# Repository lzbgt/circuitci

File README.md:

# CircuitCI

Agent-native embedded board validation runtime.

CircuitCI is a headless validation tool for embedded and IoT circuit designs. It
imports board artifacts, binds component models, runs deterministic validation
scenarios, and emits machine-readable reports that AI agents and engineers can
use before PCB fabrication.

It is not a schematic editor, PCB layout editor, or full EDA suite. The goal is
CI-style feedback for board designs: catch power, reset, boot, interface,
layout-evidence, and firmware-facing mistakes early enough that an agent or
engineer can fix the design and rerun validation.

## What It Does

- Parses Board IR YAML projects and component model libraries.
- Imports SPICE decks, KiCad XML netlists, native KiCad schematics, KiCad PCB
  placement/route evidence, JLC/EasyEDA BOM/CPL assembly evidence, Gerber
  board-outline/copper/solder-mask/solder-paste evidence, and Excellon/NC drill
  evidence.
- Suggests missing validation scenarios from board/model evidence.
- Validates power trees, regulator constraints, reset supervisors, boot straps,
  GPIO backdrive paths, I/O voltage compatibility, USB protection, USB route
  geometry, clocks, serial bootloaders, control-line sequences, and selected
  SPICE-backed analog checks.
- Writes stable JSON/Markdown reports with measurements, limits, severity, and
  suggested fixes.
- Keeps component behavior in data-driven model packs instead of hardcoding one
  MCU, USB-UART bridge, regulator, or board family into the engine.

## Current Scope

CircuitCI is currently an early Rust CLI focused on deterministic pre-fab board
validation. It already includes fixtures and model packs for common IoT-board
building blocks such as MCU boot/reset behavior, USB connectors, USB ESD
protection, LDO regulators, load switches, power muxes, battery chargers,
reset supervisors, USB-UART bridges, and level shifters.

The runtime deliberately reports limitations for areas it does not prove, such
as full USB PHY behavior, RF/antenna performance, complete PCB signal integrity,
thermal sign-off, arbitrary KiCad DRC semantics, and vendor-silicon internals.
See [docs/limitations.md](docs/limitations.md) and
[docs/common_iot_board_readiness_gaps.md](docs/common_iot_board_readiness_gaps.md).
For a concise engineering assessment of current practical value and boundaries,
see [docs/project_status_assessment.md](docs/project_status_assessment.md).
For the full-featured time/frequency-domain simulation research and backend
roadmap, see
[docs/research/circuit_simulation_full_featured/README.md](docs/research/circuit_simulation_full_featured/README.md).
For the prioritized backlog that makes CircuitCI more useful to board-validation
agents, see
[docs/agent_validation_usefulness_backlog.md](docs/agent_validation_usefulness_backlog.md).

## Install

Prerequisites:

- Rust toolchain with edition 2024 support.
- Optional: `ngspice` or `libngspice` for SPICE-backed analog scenarios.

Build:

```bash
cargo build --release
```

This creates the CLI at `target/release/circuitci`. Add it to your shell path
or call it directly from the repository:

```bash
export PATH="$PWD/target/release:$PATH"
circuitci --help
```

Run tests:

```bash
cargo test
cargo clippy --all-targets -- -D warnings
```

Optional native desktop GUI:

```bash
cargo run --features gui --bin circuitci-gui
```

The GUI is a Rust `egui`/`eframe` desktop shell with EDA-style workflow stages
for project loading, sketch/model review, scenario suggestions, validation,
simulation artifact observation, and report viewing. It uses the same engine as
the CLI and does not compile into default CLI builds. See
[docs/gui_frontend.md](docs/gui_frontend.md).

## CLI

Validate a Board IR project:

```bash
circuitci validate examples/good_power_tree_board/project.yaml \
  --output out/good_power_tree
```

Retain compact-model bundle import evidence during validation:

```bash
circuitci validate examples/good_power_tree_board/project.yaml \
  --output out/good_power_tree \
  --model-package-bundle-import \
    bundle=dist/tiny_resistor_bundle,install_dir=third_party/models/tiny_resistor,registry_output=third_party/models/compact_model_registry.json,max_runtime_ms=60000
```

Write a scenario suggestion artifact:

```bash
circuitci suggest-scenarios examples/scenario_suggestions_usb_connector_protection/project.yaml \
  --output out/scenario_suggestions.yaml
```

Add profile-coverage remediation templates for missing `iot_basic_v0` core
checks:

```bash
circuitci suggest-scenarios examples/good_backdrive_fixed_board/project.yaml \
  --profile iot_basic_v0 \
  --output out/profile_suggestions.yaml
```

Import a KiCad schematic:

```bash
circuitci import-kicad-schematic path/to/root.kicad_sch \
  --mapping path/to/circuitci.kicad-map.yaml \
  --output out/imported.project.yaml
```

Enrich an imported project with KiCad PCB placement and route evidence:

```bash
circuitci import-kicad-pcb path/to/board.kicad_pcb \
  --project out/imported.project.yaml \
  --output out/imported_with_layout.project.yaml
```

Import JLC/EasyEDA assembly BOM and placement evidence:

```bash
circuitci import-jlc-assembly \
  --bom path/to/bom.csv \
  --placement path/to/placement.csv \
  --output out/imported_assembly.project.yaml
```

Inspect an EasyEDA Pro `.eprj2` SQLite project envelope:

```bash
circuitci inspect-easyeda-pro path/to/project.eprj2 \
  --output out/easyeda_pro_inspection.md
```

Append EasyEDA/JLC flying-probe pad and net evidence:

```bash
circuitci import-easyeda-flying-probe path/to/FlyingProbeTesting.json \
  --project out/imported_assembly.project.yaml \
  --output out/imported_with_probe_pads.project.yaml
```

Enrich an imported project with Gerber board-outline evidence:

```bash
circuitci import-gerber-outline path/to/Gerber_BoardOutlineLayer.GKO \
  --project out/imported_assembly.project.yaml \
  --output out/imported_with_outline.project.yaml
```

Append Gerber copper evidence:

```bash
circuitci import-gerber-copper path/to/Gerber_TopLayer.GTL \
  --project out/imported_with_outline.project.yaml \
  --output out/imported_with_copper.project.yaml
```

Append Gerber solder-mask evidence:

```bash
circuitci import-gerber-solder-mask path/to/Gerber_TopSolderMaskLayer.GTS \
  --project out/imported_with_copper.project.yaml \
  --output out/imported_with_mask.project.yaml
```

Append Gerber solder-paste evidence:

```bash
circuitci import-gerber-solder-paste path/to/Gerber_TopPasteMaskLayer.GTP \
  --project out/imported_with_mask.project.yaml \
  --output out/imported_with_paste.project.yaml
```

Append Excellon/NC drill evidence:

```bash
circuitci import-excellon-drill path/to/Drill_PTH_Through.DRL \
  --project out/imported_with_paste.project.yaml \
  --output out/imported_with_drills.project.yaml

circuitci import-excellon-drill path/to/Drill_PTH_Through_Via.DRL \
  --project out/imported_with_drills.project.yaml \
  --output out/imported_with_drills_and_vias.project.yaml
```

Attach explicit order/manufacturing metadata when those values are known from
the fabrication order, stencil order, or another reviewed process record:

```bash
circuitci set-manufacturing-metadata out/imported_with_drills_and_vias.project.yaml \
  --output out/imported_with_order_metadata.project.yaml \
  --stencil-thickness-mm 0.10 \
  --min-drill-edge-clearance-mm 0.50 \
  --min-slot-edge-clearance-mm 0.50 \
  --min-paste-area-ratio 0.70 \
  --max-paste-area-ratio 1.00 \
  --min-solder-paste-spacing-mm 0.15 \
  --source jlc_order_metadata
```

Or import the same reviewed facts from a source CSV while preserving row-level
evidence in a JSON manifest. Repeated `field=controlled_impedance_net` and
`field=controlled_impedance_pair` rows create or replace reviewed
`board.manufacturing.controlled_impedance` targets, including optional
solder-mask loading metadata, repeated `field=controlled_impedance_coupon`
rows create or replace reviewed fabricator coupon measurement evidence that
validation maps back to matching reviewed board impedance targets, repeated
`field=controlled_impedance_coupon_sample` rows attach reviewed coupon batch
sample measurements under named coupons, and coupon rows can carry reviewed
lot/panel/stackup plus trace layer/width/gap correlation metadata. Repeated
`field=controlled_impedance_solver_result` rows create or replace reviewed
source-backed solver-result evidence under
`board.manufacturing.controlled_impedance.solver_results[]`, and repeated
`field=controlled_impedance_solver_sample` rows attach reviewed solver
sweep/corner samples under named solver results. Solver-result rows can also
carry reviewed signed-artifact URI/digest/signer metadata, input-deck
URI/digest, output-schema URI/digest, reviewed solver configuration-lock
URI/digest/tool/revision metadata, reviewed runtime allowlist/profile/options
metadata, reviewed license/feature entitlement metadata, reviewed execution
environment lock/fingerprint metadata, reviewed run-log/random-seed/numeric
tolerance metadata, setup metadata, copper-roughness metadata,
etch-compensation metadata, and material-library
metadata for consistency screening. Repeated
`field=controlled_impedance_solver_material_corner` rows attach reviewed
dielectric material/corner evidence under named solver results, tying required
solver corners back to explicit stackup material metadata. Repeated
`field=controlled_impedance_solver_material_library` rows record reviewed
material-library artifact content and required field coverage, and repeated
`field=controlled_impedance_solver_material_acceptance` rows record reviewed
fabricator acceptance of solver material library/revision and stackup revision
coverage. Repeated `field=controlled_impedance_solver_material_process` rows
record reviewed material lot/process drift evidence for solver material
library/revision, fabricator stackup revision, dielectric layer, and material.
Repeated `field=controlled_impedance_solver_runtime_allowlist` rows record
reviewed runtime option allowlists for a solver and configuration-lock
revision.
Repeated `field=controlled_impedance_solver_entitlement` rows record reviewed
solver license/feature entitlement evidence for a solver and tool version.
Repeated `field=controlled_impedance_solver_execution_environment` rows record
reviewed solver execution environment lock evidence, including artifact
provenance, a reproducibility fingerprint, and locked component names.
Repeated `field=controlled_impedance_solver_run_log` rows record reviewed
solver run-log reproducibility evidence, including artifact provenance, run
id, random seed, numeric tolerance policy, residual limit, and iteration
limit. Optional rerun limits on that row can require reviewed deterministic
rerun samples imported with repeated `field=controlled_impedance_solver_rerun`
rows. Optional convergence-window limits on the run-log row can require
reviewed solver convergence samples imported with repeated
`field=controlled_impedance_solver_convergence_sample` rows, including
stopping criteria, residual, iteration, artifact URI, and artifact digest
evidence. A run-log row can also opt into monotonic residual trend evidence
with `require_monotonic_residual_decrease`, and can carry reviewed numerical
precision policy provenance such as floating-point format, significant digits,
roundoff budget, artifact URI, and artifact digest.
Repeated
`field=controlled_impedance_solver_qualification` rows create or replace
reviewed solver tool/version qualification evidence. Repeated
`field=thermal_copper` rows create or replace reviewed
`board.manufacturing.thermal_copper[]` policy entries, and repeated
`field=thermal_measurement` rows append reviewed measured-temperature evidence
under `board.manufacturing.thermal_measurements[]`. Repeated
`field=thermal_package` rows create or replace reviewed component package
thermal metadata under `board.manufacturing.thermal_packages[]`. Repeated
`field=thermal_environment` rows create or replace reviewed operating
environment evidence under `board.manufacturing.thermal_environments[]`.
Repeated `field=thermal_limit` rows create or replace reviewed measured and
package temperature limits under `board.manufacturing.thermal_limits[]`.
Repeated
`field=stackup_layer` rows create or replace reviewed
`board.layout.stackup.layers[]` entries so stackup evidence can travel with
fabrication/order metadata without hand-authored YAML. Repeated
`field=rf_antenna_keepout`, `field=rf_antenna_feed_path`,
`field=rf_antenna_matching_network`, `field=rf_antenna_measurement`, and
`field=rf_antenna_performance_limit` rows create or replace reviewed RF
antenna layout/topology/measurement/limit constraints, including optional
sampled sweep-coverage policy and measurement-condition evidence, under
`board.layout.constraints.rf_antenna`:

```bash
circuitci import-manufacturing-metadata \
  --project out/imported_with_drills_and_vias.project.yaml \
  --metadata order_metadata.csv \
  --output out/imported_with_order_metadata.project.yaml \
  --source jlc_order_metadata \
  --allow-unknown-fields
```

`suggest-scenarios` consumes these Board IR fields to make matching
manufacturing templates runnable without turning order-specific limits into
global process defaults.

Run an acceptance suite:

```bash
circuitci validate-suite suites/um_stm32l4_downloader_acceptance.yaml \
  --output out/acceptance
```

## Project Model

CircuitCI uses a normalized Board IR:

```text
project.yaml / KiCad / SPICE
  -> Board Graph IR
  -> component model binding
  -> scenario execution
  -> validation rules and optional SPICE backend
  -> JSON + Markdown reports
```

Important contracts:

- [docs/current_capabilities.md](docs/current_capabilities.md)
- [docs/board_ir.md](docs/board_ir.md)
- [docs/component_model_contract.md](docs/component_model_contract.md)
- [docs/scenario_language.md](docs/scenario_language.md)
- [docs/fabrication_process_presets.md](docs/fabrication_process_presets.md)
- [docs/manufacturing_metadata_importer.md](docs/manufacturing_metadata_importer.md)
- [docs/gui_frontend.md](docs/gui_frontend.md)
- [docs/report_schema.md](docs/report_schema.md)
- [docs/scenario_suggestions.md](docs/scenario_suggestions.md)

## Repository Layout

```text
src/
  board_ir/       Board IR parsing and normalized project types
  cli/            Command-line entry points
  gui.rs          Optional Rust desktop frontend behind the gui feature
  importers/      KiCad, SPICE, and layout-evidence importers
  library/        Component model loading and binding
  reports/        JSON and Markdown report generation
  validation/     Deterministic rule implementations

libs/
  generic/        Generic component models
  vendor/         Datasheet-backed vendor model packs

models/spice/     SHA-pinned SPICE model cards and generic behavioral
                  macro-model libraries used by generated analog scenarios
examples/         Passing/failing fixtures and importer demos
schemas/          JSON schemas for Board IR and reports
suites/           Acceptance-suite manifests
tests/            CLI and integration regressions
docs/             Engineering contracts and research notes
```

## Validation Philosophy

CircuitCI is conservative:

- A rule fails closed when required evidence is missing.
- Reports distinguish proven failures from low-confidence or unmodeled areas.
- Datasheet-backed component packs record their source artifacts and modeled
  facts.
- Suggestions never invent observations such as reset-release timestamps,
  strap states, protection resistance, load-switch enable state, or board layout
  limits.

## License

MIT. See [LICENSE](LICENSE).

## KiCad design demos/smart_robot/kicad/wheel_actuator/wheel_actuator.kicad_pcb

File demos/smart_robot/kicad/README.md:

# Smart Robot KiCad CAD Bridge

This folder contains KiCad-source artifacts that are meant to be imported back
through CircuitCI during schematic/layout iteration.

## Motion Core

`motion_core/root.kicad_sch` is the first KiCad schematic skeleton for the
validated motion-core logical model. It intentionally uses local `CircuitCI:*`
symbols with named pins so agents can edit connectivity without depending on a
complete production symbol library yet.

`motion_core/circuitci.kicad-map.yaml` binds those schematic references and
pins back to the same source-backed models used by
`../circuitci/motion_core/project.yaml`.

Current scope:

- LicheeRV Nano purchased module interface.
- AT32F435 motion MCU.
- ICM-42688-P IMU SPI/interrupt link.
- TCAN3413 CAN transceiver.
- THVD1450 RS485 transceiver.
- ESD2CAN24-Q1 and ESDS552 static bus TVS devices.
- 120 ohm CAN and RS485 endpoint termination options.

Import check:

```sh
circuitci import-kicad-schematic \
  demos/smart_robot/kicad/motion_core/root.kicad_sch \
  --mapping demos/smart_robot/kicad/motion_core/circuitci.kicad-map.yaml \
  --output out/smart_robot_motion_core_imported.project.yaml
```

The imported Board IR is a connectivity source artifact. It does not yet carry
all fields from the richer logical validation model, such as `power_domains`,
validation scenarios, pre-layout placement contracts, or routed PCB evidence.
Keep using `../circuitci/motion_core/project.yaml` for sign-off checks until
the KiCad importer round-trips those fields or explicit overlay steps are
added.

## Wheel Actuator

`wheel_actuator/root.kicad_sch` is the matching KiCad connectivity skeleton for
the reusable left/right wheel actuator board. It uses local `CircuitCI:*`
symbols for the motor-control MCU, DRV8323 gate driver, CAN transceiver and TVS,
endpoint termination option, encoder/Hall input, preliminary CSD88599Q5DC
three-phase bridge candidate, phase shunts, motor-load envelope, regeneration
absorber envelope, and JST VH actuator-bus connector.

`wheel_actuator/circuitci.kicad-map.yaml` binds those schematic references and
pins back to the source-backed models used by
`../circuitci/wheel_actuator/project.yaml`. It also carries the
`MODEL_QUALITY_REQUIRED` sign-off scenario for `M1`, plus the
`LOAD_CABLE_CURRENT_VALID`, `LOAD_CABLE_THERMAL_DERATING_VALID`, and
`LOAD_CABLE_VOLTAGE_DROP_VALID` actuator-bus harness gates. The imported
schematic carries selected JST VH/AWG16 harness current and loop-resistance
evidence and selected Vishay RH100 first-pass regen absorber evidence, but
still blocks fabrication until the placeholder motor and cable
temperature-rise evidence are replaced by selected datasheet or measured
evidence.

`wheel_actuator/wheel_actuator.kicad_pcb` is the first smart-robot PCB layout
bridge. It is a compact placement/routing artifact for import testing: it
contains component placements, JACT1 CAN and power pads, CAN ESD/termination
placement, preliminary motor bridge, phase-shunt and motor pads, CAN routes,
motor power/phase routes, current-sense routes, a ground zone, and explicit
net-class constraints.

Import check:

```sh
circuitci import-kicad-schematic \
  demos/smart_robot/kicad/wheel_actuator/root.kicad_sch \
  --mapping demos/smart_robot/kicad/wheel_actuator/circuitci.kicad-map.yaml \
  --output out/smart_robot_wheel_actuator_imported.project.yaml

circuitci import-kicad-pcb \
  demos/smart_robot/kicad/wheel_actuator/wheel_actuator.kicad_pcb \
  --project out/smart_robot_wheel_actuator_imported.project.yaml \
  --output out/smart_robot_wheel_actuator_with_pcb.project.yaml
```

As with the motion-core bridge, the imported schematic Board IR proves
connectivity and model binding only. The PCB-enriched Board IR additionally
proves first-pass placement, pad, route, via, outline, zone, and routing-rule
evidence. The imported route widths now also drive the wheel actuator CAN
placement checks and first-pass motor phase/`VBAT_SW` route-current checks. It
also drives the first-pass phase-shunt and current-sense route placement
checks. It is still not a final layout sign-off: it does not prove MOSFET
SOA/thermal margins, dynamic current-sense waveform behavior, copper
temperature rise, selected regeneration absorber behavior, repeated-pulse
heating, selected cable assembly current/thermal/drop behavior, EMC, or
manufacturing DRC.

## PMU

`pmu/root.kicad_sch` is the KiCad connectivity skeleton for the reusable PMU
board. It uses local `CircuitCI:*` symbols for the USB-C PD source placeholder,
protected 2S battery source, BQ25798 charger, TPS54331 5 V buck, TPS62162
3.3 V buck, required 3.3 V support passives, selected TPS25948 servo switch,
selected TPS24751/CSD17501Q5A wheel switch path, and the first-pass rail load
budgets.

`pmu/circuitci.kicad-map.yaml` binds those schematic references and pins back
to the source-backed models used by `../circuitci/pmu/project.yaml`. It also
preserves the selected TPS25948 model for `U_SERVO_SW`, the selected
TPS24751/CSD17501Q5A path for `U_WHEEL_SW`, and the
`MODEL_QUALITY_REQUIRED` gate for both switched rails. It
also preserves the `POWER_SWITCH_BUDGET_VALID`, reverse-current, and inrush
gates, so imported schematics cannot bypass selected-part current-limit,
static thermal, reverse-mode, and soft-start evidence requirements.

Import check:

```sh
circuitci import-kicad-schematic \
  demos/smart_robot/kicad/pmu/root.kicad_sch \
  --mapping demos/smart_robot/kicad/pmu/circuitci.kicad-map.yaml \
  --output out/smart_robot_pmu_imported.project.yaml
```

The imported Board IR proves PMU connectivity, passive values, and the
selected-switch sign-off gate only. It does not yet round-trip the BQ25798
configured charge current, power-domain metadata, e-stop pin states, regulator
layout contracts, selected-switch current/thermal behavior, or routed PCB
evidence.

## Servo Payload

`servo_payload/root.kicad_sch` is the KiCad connectivity skeleton for the
low-load PWM servo/payload board. It uses local `CircuitCI:*` symbols for the
AT32F435 I2C/OE host pins, PCA9685 PWM driver, four low-load servo design
loads, and four JST XH servo headers.

`servo_payload/circuitci.kicad-map.yaml` binds those schematic references and
pins back to the source-backed models used by
`../circuitci/servo_payload/project.yaml`.

Import check:

```sh
circuitci import-kicad-schematic \
  demos/smart_robot/kicad/servo_payload/root.kicad_sch \
  --mapping demos/smart_robot/kicad/servo_payload/circuitci.kicad-map.yaml \
  --output out/smart_robot_servo_payload_imported.project.yaml
```

The imported Board IR proves I2C, OE, PWM fanout, servo power, and connector
signal connectivity only. It does not yet round-trip connector-current budget
scenarios, servo stall/regeneration assumptions, cable assembly derating, or
routed PCB evidence.

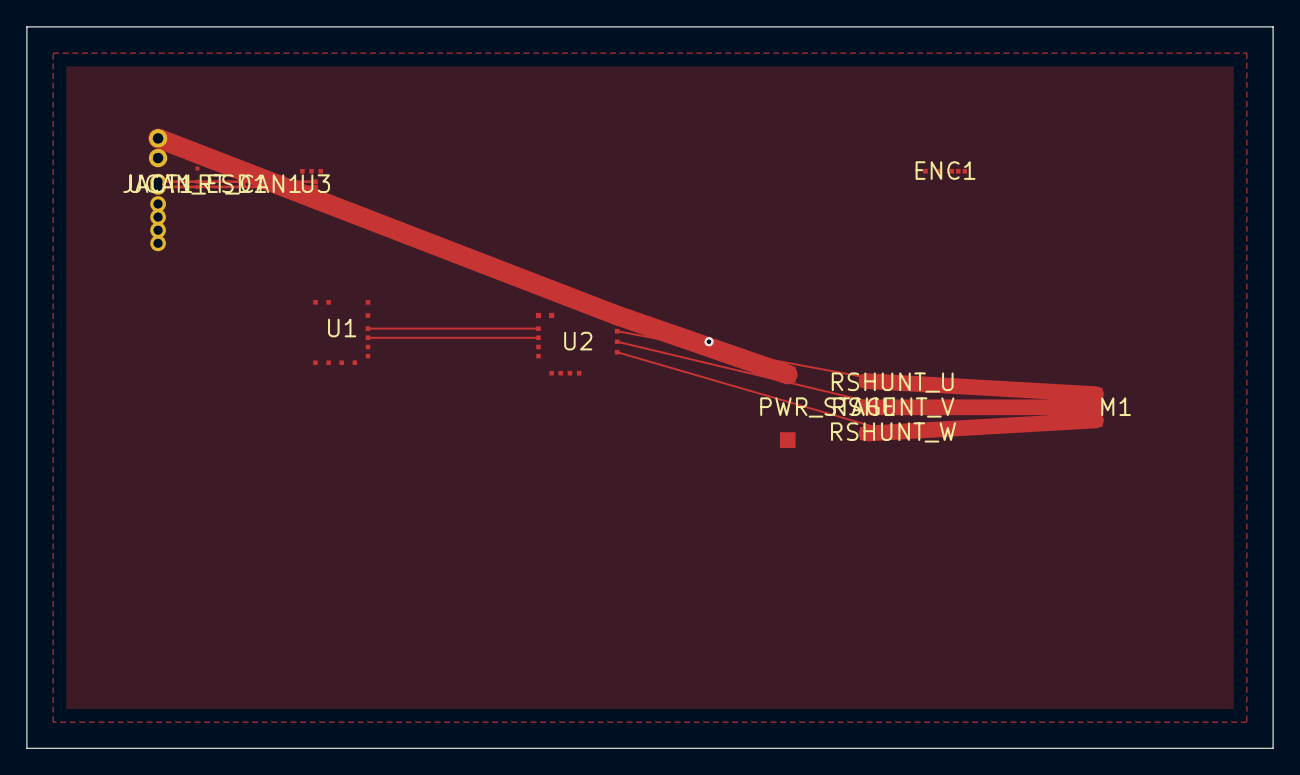
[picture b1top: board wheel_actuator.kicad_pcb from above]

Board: 0 copper layers, 95.0 x 55.0 mm, 12 parts (0 on the bottom side), 21 nets.

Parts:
ENC1: ENCODER_OR_HALL_3V3; Encoder_Hall_3V3
JACT1: B8P-VH_ACTUATOR_BUS; JST_VH_8Pin_Actuator_Bus
M1: WHEEL_MOTOR_DESIGN_ENVELOPE; Wheel_Motor_Envelope
PWR_STAGE: 3x_CSD88599Q5DC_PRELIMINARY; CSD88599Q5DC_3Phase_Bridge
RSHUNT_U: 5mR_1W; Phase_Shunt_5mR
RSHUNT_V: 5mR_1W; Phase_Shunt_5mR
RSHUNT_W: 5mR_1W; Phase_Shunt_5mR
RT_CAN1: 120R; CAN_Termination
U1: AT32M416; AT32M416_Motor_Control
U2: DRV8323
U3: TCAN3413DR; TCAN3413
UCAN_ESD1: ESD2CAN24-Q1; ESD2CAN24_Q1

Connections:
3v3_logic: ENC1.VCC, U1.VDD, U2.DVDD, U3.VCC, U3.VIO
cur_u: RSHUNT_U.B, U2.SOA
cur_v: RSHUNT_V.B, U2.SOB
cur_w: RSHUNT_W.B, U2.SOC
drv_enable: U1.DRV_EN, U2.ENABLE
drv_inha: U1.PWM_UH, U2.INHA
drv_inhb: U1.PWM_VH, U2.INHB
drv_inhc: U1.PWM_WH, U2.INHC
drv_inla: U1.PWM_UL, U2.INLA
drv_inlb: U1.PWM_VL, U2.INLB
drv_inlc: U1.PWM_WL, U2.INLC
drv_nfault: U1.DRV_NFAULT, U2.NFAULT
gnd: ENC1.GND, JACT1.GND, PWR_STAGE.GND, U1.GND, U2.GND, U3.GND, UCAN_ESD1.GND
phase_u: M1.PHASE_U, PWR_STAGE.PHASE_U, RSHUNT_U.A
phase_v: M1.PHASE_V, PWR_STAGE.PHASE_V, RSHUNT_V.A
phase_w: M1.PHASE_W, PWR_STAGE.PHASE_W, RSHUNT_W.A
robot_canh: JACT1.CANH, RT_CAN1.A, U3.CANH, UCAN_ESD1.CANH
robot_canl: JACT1.CANL, RT_CAN1.B, U3.CANL, UCAN_ESD1.CANL
vwheel_sw: JACT1.VBAT, PWR_STAGE.VM, U2.VM
wheel_can_rx: U1.CAN_RX, U3.RXD
wheel_can_tx: U1.CAN_TX, U3.TXD

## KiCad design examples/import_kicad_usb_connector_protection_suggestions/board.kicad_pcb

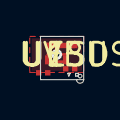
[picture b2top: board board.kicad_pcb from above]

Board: 0 copper layers, 2.4 x 2.4 mm, 4 parts (0 on the bottom side), 4 nets.

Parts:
H1: NPTH
J1: USB2_CONNECTOR; USB2
UESD: TPD2EUSB30
UVBUS: VBUS_ESD

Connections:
GND: J1.GND, J1.SHIELD, UESD.GND, UVBUS.GND
USB_DM: J1.D-, UESD.D1-
USB_DP: J1.D+, UESD.D1+
USB_VBUS: J1.VBUS, UVBUS.IO

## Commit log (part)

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2026-06-28 Add missing-net YAML repair
2026-06-28 Add stray-pin YAML repair
2026-06-28 Report blocked YAML repairs
2026-06-28 Add YAML repair dry-run mode
2026-06-28 Add report-driven YAML repair apply
2026-06-28 Add selective YAML repair proposal apply
2026-06-28 Add required-pin YAML repair
2026-06-28 Add YAML repair reason codes
2026-06-28 Preserve EasyEDA pad source evidence
2026-06-28 Add EasyEDA Pro inspection manifest
2026-06-28 Add JLC assembly import manifest
2026-06-28 Add KiCad footprint semantic evidence
2026-06-28 Sync footprint import backlog
2026-06-28 Preserve KiCad pad fabrication overrides
2026-06-28 Add EasyEDA Pro structure object evidence
2026-06-28 Classify EasyEDA Pro plaintext payload shapes
2026-06-28 Add manufacturing metadata CSV import
2026-06-28 Add JLC assembly orientation evidence
2026-06-28 Preserve KiCad footprint property evidence
2026-06-28 Add assembly footprint alignment validation
2026-06-28 Suggest assembly footprint alignment checks
2026-06-28 Add pin 1 orientation validation
2026-06-28 Add conductor creepage clearance validation
2026-06-28 Add controlled impedance geometry validation
2026-06-28 Add adjacent plane return path validation
2026-06-28 Suggest adjacent plane return path checks
2026-06-28 Add reference plane slot crossing validation
2026-06-28 Suggest reference plane slot crossing checks
2026-06-28 Add return path stitching via validation
2026-06-28 Suggest return path stitching via checks
2026-06-28 Suggest controlled impedance geometry checks
2026-06-28 Split manufacturing route physics suggestions
2026-06-28 Split manufacturing scenario suggestion tests
2026-06-28 Add controlled impedance stackup evidence checks
2026-06-28 Add RF antenna keepout validation
2026-06-28 Add RF antenna feed path validation
2026-06-28 Add thermal copper area validation
2026-06-28 Add thermal via stackup validation
2026-06-28 Add thermal package temperature validation
2026-06-28 Add measured thermal validation evidence
2026-06-28 Add thermal via plating validation
2026-06-28 Split thermal manufacturing modules
2026-06-28 Add thermal measurement uncertainty margins
2026-06-28 Add thermal derating environment validation
2026-06-28 Add thermal via plating thickness evidence
2026-06-28 Add thermal via barrel cross-section validation
2026-06-28 Add thermal copper metadata CSV import
2026-06-28 Add controlled impedance metadata CSV import
2026-06-28 Split manufacturing metadata row parsing
2026-06-28 Add stackup layer metadata CSV import
2026-06-28 Add RF antenna metadata CSV import
2026-06-28 Split manufacturing metadata CSV parsing
2026-06-28 Split manufacturing metadata row families
2026-06-28 Add reviewed thermal package metadata import
2026-06-28 Check conflicting thermal package metadata
2026-06-28 Add thermal environment metadata import
2026-06-28 Add thermal limit metadata import
2026-06-28 Add RF measured performance validation
2026-06-28 Add RF antenna measurement metadata import
2026-06-28 Add RF matching topology validation
2026-06-28 Add RF matching metadata CSV import
2026-06-28 Update RF layout physics backlog
2026-06-28 Add RF performance limit metadata import
2026-06-28 Add RF sweep performance evidence
2026-06-28 Split RF antenna measurement validation
2026-06-28 Add RF measurement condition evidence
2026-06-29 Split RF antenna scenario suggestions
2026-06-29 Add controlled impedance solder mask validation
2026-06-29 Add controlled impedance coupon validation
2026-06-29 Split RF manufacturing metadata tests
2026-06-29 Improve imported schematic readability
2026-06-29 Map impedance coupons to board targets
2026-06-29 Clarify impedance coupon mapping guidance
2026-06-29 Add impedance coupon batch validation
2026-06-29 Add impedance coupon trace correlation validation
2026-06-29 Add controlled impedance solver result validation
2026-06-29 Split controlled impedance suggestions
2026-06-29 Add solver artifact provenance evidence
2026-06-29 Add impedance solver sweep evidence
2026-06-29 Add solver input deck consistency evidence
2026-06-29 Add solver copper roughness consistency evidence
2026-06-29 Add solver etch compensation consistency evidence
2026-06-29 Add solver qualification evidence
2026-06-29 Split thermal manufacturing metadata tests
2026-06-29 Add solver artifact signature evidence
2026-06-29 Add solver material library evidence
2026-06-29 Split Board IR manufacturing types
2026-06-29 Add solver material corner evidence
2026-06-29 Split solver metadata validation
2026-06-29 Split controlled impedance solver suggestions
2026-06-29 Add solver stackup signoff evidence
2026-06-29 Improve high-pin schematic label readability
2026-06-29 Add deterministic Sketch SVG export
2026-06-29 Add solver material library content evidence
2026-06-29 Add solver material acceptance evidence
2026-06-29 Add solver material process drift evidence
2026-06-29 Add solver material artifact field coverage
2026-06-29 Add solver output schema evidence
2026-06-29 Add solver config lock evidence
2026-06-29 Add solver runtime allowlist evidence
2026-06-29 Add solver entitlement evidence
2026-06-29 Add solver execution environment evidence
2026-06-29 Add solver run log reproducibility evidence
2026-06-29 Add solver deterministic rerun evidence
2026-06-29 Add solver convergence window evidence
2026-06-29 Add solver residual trend evidence
2026-06-29 Add solver numerical precision evidence
2026-06-29 Split manufacturing metadata row validation
2026-06-29 Split RF manufacturing metadata row parsing
2026-06-29 Split controlled impedance solver tests
2026-06-29 Split solver manufacturing metadata tests
2026-06-29 Split RF manufacturing metadata value mapping
2026-06-29 Split GUI analog helper modules
